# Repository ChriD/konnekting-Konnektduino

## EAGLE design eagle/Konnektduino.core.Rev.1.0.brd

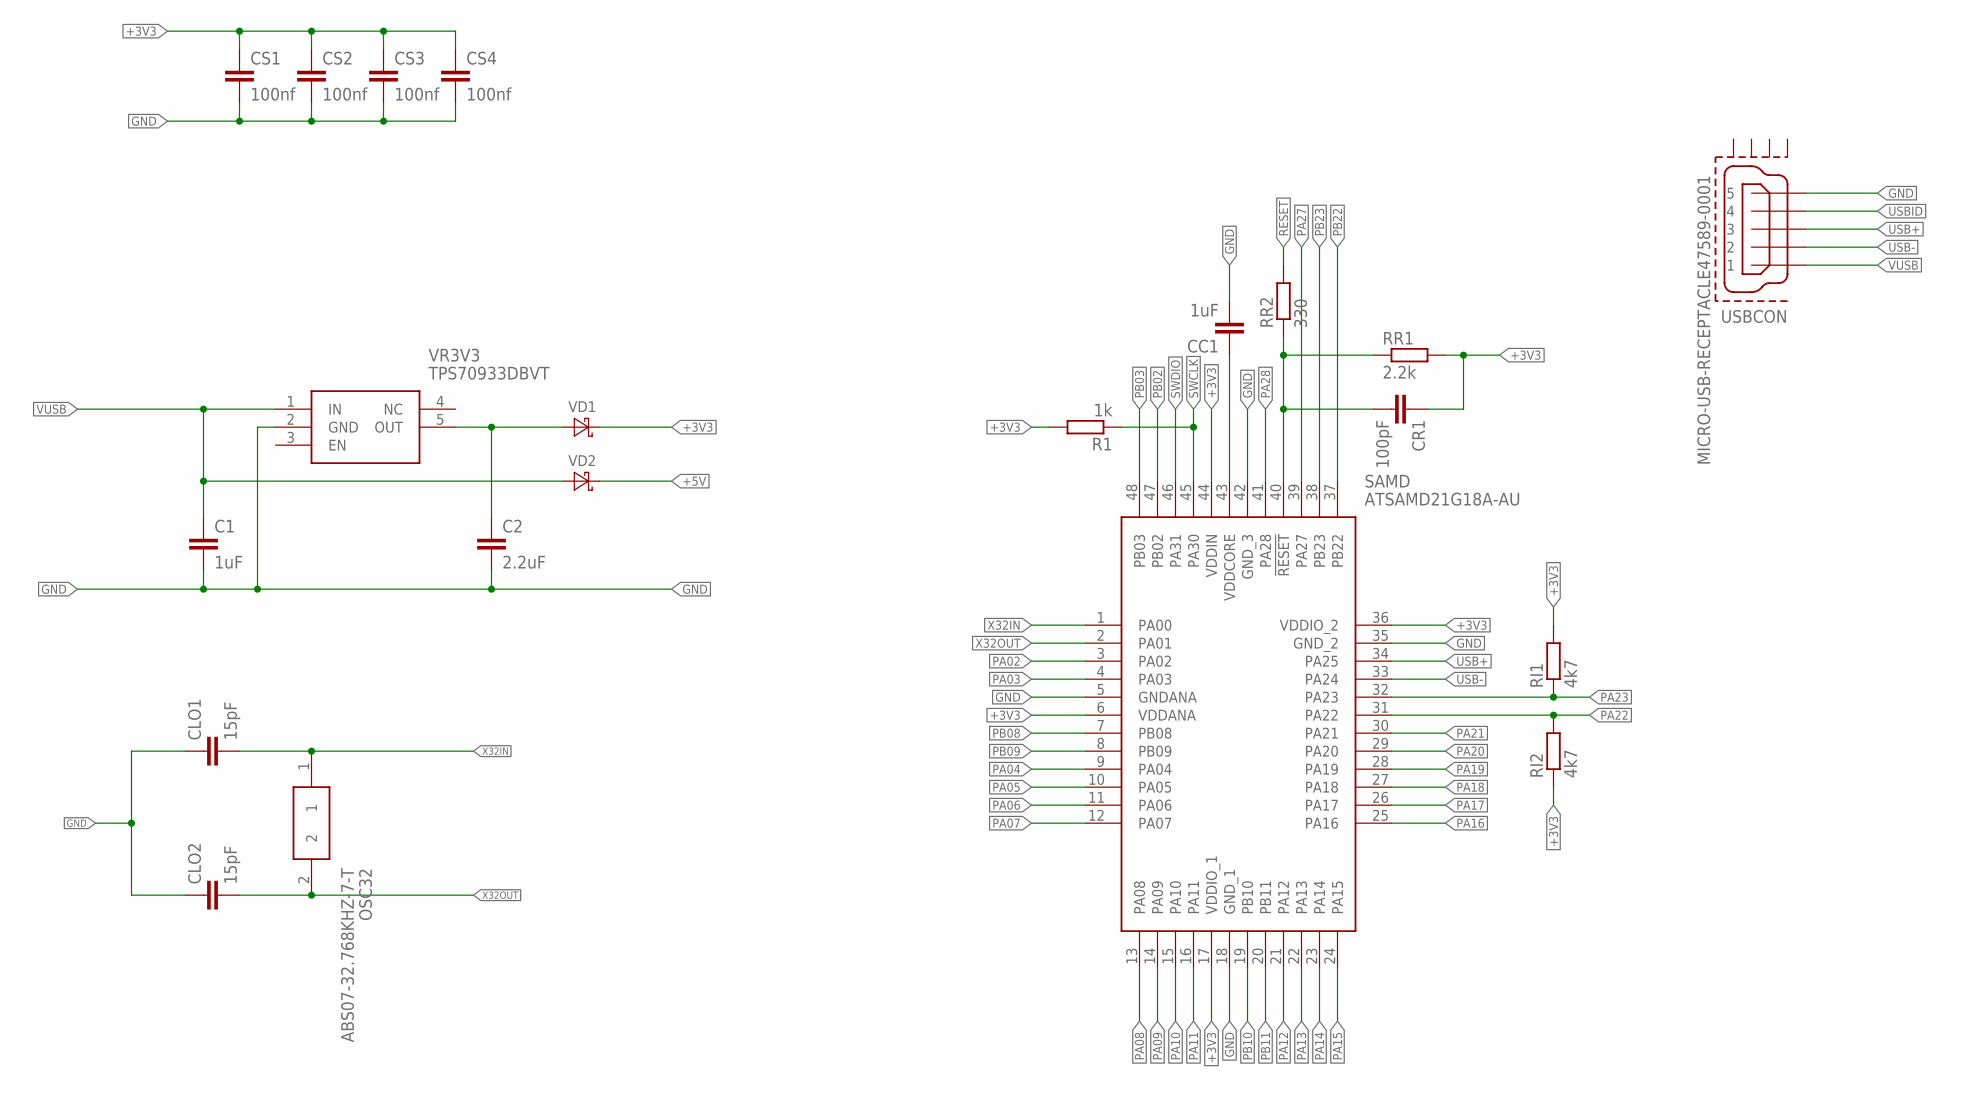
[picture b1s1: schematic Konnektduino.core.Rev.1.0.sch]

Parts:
C1: 1uF; C0603
C2: 2.2uF; C0603
CC1: 1uF; C0603
CLO1, CLO2: 15pF; C0603
CR1: 100pF; C0603
CS1, CS2, CS3, CS4: 100nf; C0603
OSC32: ABS07-32.768KHZ-7-T; ABS-07
R1: 1k; R0603
RI1, RI2: 4k7; R0603
RR1: 2.2k; R0603
RR2: 330; R0603
SAMD: ATSAMD21G18A-AU; QFP50P900X900X120-48N
USBCON: MICRO-USB-RECEPTACLE47589-0001; 47589-0001
VD1, VD2: DIODE-SCHOTTKY-0603; D0603
VR3V3: TPS70933DBVT; SOT95P280X145-5N

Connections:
+3V3: CR1.1, CS1.1, CS2.1, CS3.1, CS4.1, R1.2, RI1.2, RI2.1, RR1.2, SAMD.6 (VDDANA), SAMD.17 (VDDIO_1), SAMD.36 (VDDIO_2), SAMD.44 (VDDIN), VD1.C
+5V: VD2.C
GND: C1.2, C2.2, CC1.2, CLO1.1, CLO2.1, CS1.2, CS2.2, CS3.2, CS4.2, SAMD.5 (GNDANA), SAMD.18 (GND_1), SAMD.35 (GND_2), SAMD.42 (GND_3), USBCON.5, VR3V3.2 (GND)
unnamed: C2.1, VD1.A, VR3V3.5 (OUT)
NRST: CR1.2, RR1.1, RR2.1, SAMD.40 (!RESET)
PA02: SAMD.3 (PA02)
PA03: SAMD.4 (PA03)
PA04: SAMD.9 (PA04)
PA05: SAMD.10 (PA05)
PA06: SAMD.11 (PA06)
PA07: SAMD.12 (PA07)
PA08: SAMD.13 (PA08)
PA09: SAMD.14 (PA09)
PA10: SAMD.15 (PA10)
PA11: SAMD.16 (PA11)
PA12: SAMD.21 (PA12)
PA13: SAMD.22 (PA13)
PA14: SAMD.23 (PA14)
PA15: SAMD.24 (PA15)
PA16: SAMD.25 (PA16)
PA17: SAMD.26 (PA17)
PA18: SAMD.27 (PA18)
PA19: SAMD.28 (PA19)
PA20: SAMD.29 (PA20)
PA21: SAMD.30 (PA21)
PA22: RI2.2, SAMD.31 (PA22)
PA23: RI1.1, SAMD.32 (PA23)
PA27: SAMD.39 (PA27)
PA28: SAMD.41 (PA28)
PB02: SAMD.47 (PB02)
PB03: SAMD.48 (PB03)
PB08: SAMD.7 (PB08)
PB09: SAMD.8 (PB09)
PB10: SAMD.19 (PB10)
PB11: SAMD.20 (PB11)
PB22: SAMD.37 (PB22)
PB23: SAMD.38 (PB23)
RESET: RR2.2
SWCLK: R1.1, SAMD.45 (PA30)
SWDIO: SAMD.46 (PA31)
USB+: SAMD.34 (PA25), USBCON.3
USB-: SAMD.33 (PA24), USBCON.2
USBID: USBCON.4
VDDCORE: CC1.1, SAMD.43 (VDDCORE)
VUSB: C1.1, USBCON.1, VD2.A, VR3V3.1 (IN)
X32IN: CLO1.2, OSC32.1, SAMD.1 (PA00)
X32OUT: CLO2.2, OSC32.2, SAMD.2 (PA01)

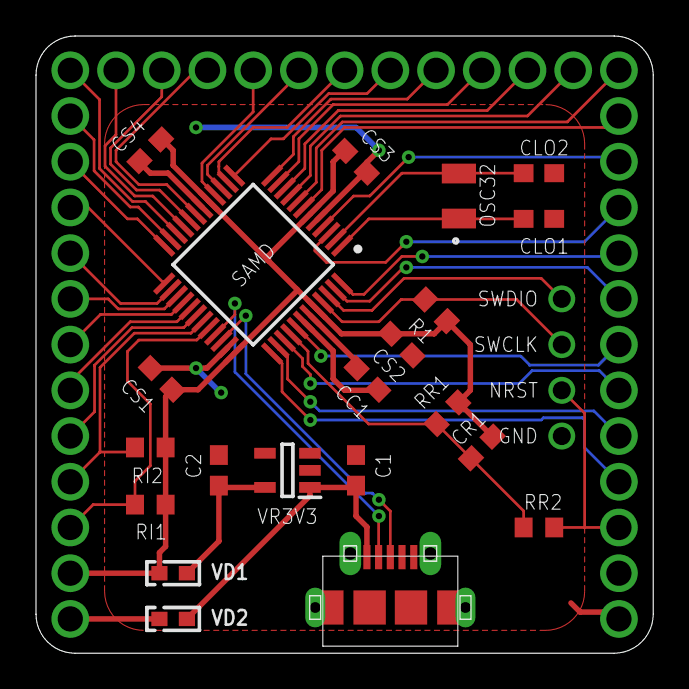
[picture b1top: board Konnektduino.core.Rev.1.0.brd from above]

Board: 2 copper layers, 34.3 x 34.3 mm, 21 parts (0 on the bottom side), 13 nets.

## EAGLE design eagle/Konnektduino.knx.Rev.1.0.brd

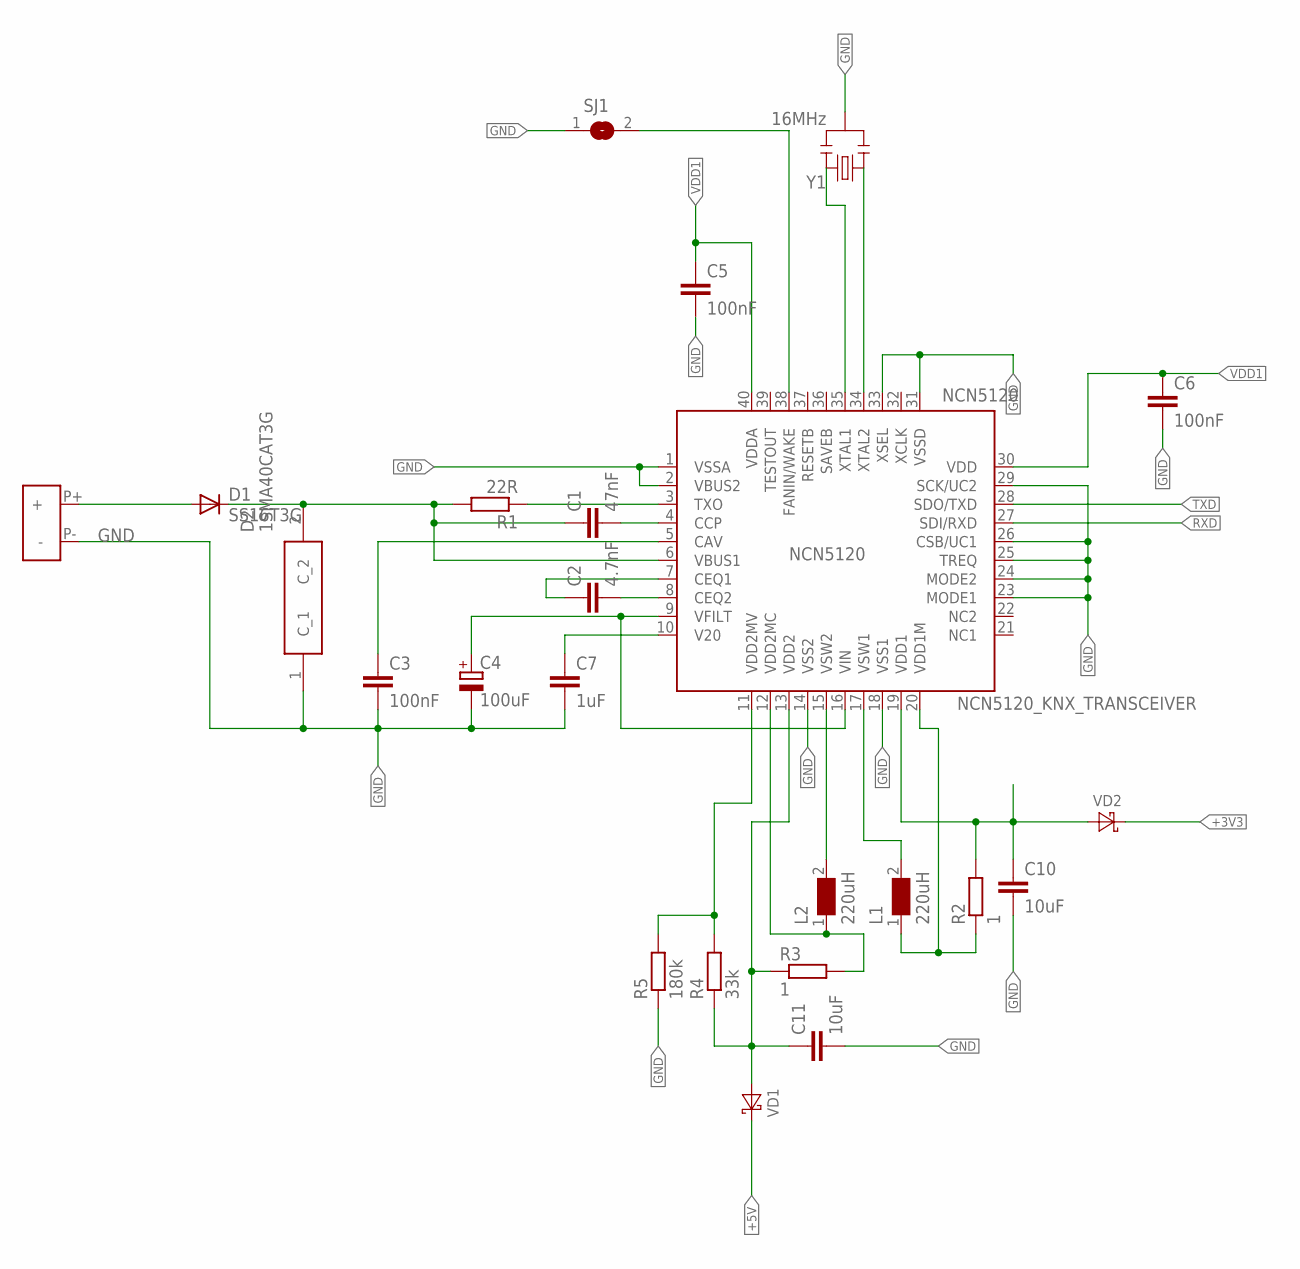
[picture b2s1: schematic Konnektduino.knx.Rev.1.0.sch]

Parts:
C1: 47nF; C0603
C2: 4.7nF; C0603
C3, C5, C6: 100nF; C0603
C4: 100uF; PANASONIC_E
C7: 1uF; C0603
C10, C11: 10uF; C0603
D1: SS16T3G; SMA-DIODE_ALT
D2: 1SMA40CAT3G; DIONM5226X220N
L1, L2: 220uH; WE-PD2_7850
NCN5120: NCN5120_KNX_TRANSCEIVER; QFN40
R1: 22R; R1218
R2, R3: 1; R0603
R4: 33k; R0603
R5: 180k; R0603
SJ1: SJW
U$2: KNX_KLEMME
VD1, VD2: DIODE-SCHOTTKY-0603; D0603
Y1: 16MHz; RESONATOR-SMD

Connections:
+3V3: VD2.C
+5V: VD1.C
GND: C3.2, C4.-, C5.2, C6.2, C7.2, C10.2, C11.2, D2.1 (C_1), NCN5120.1 (VSSA), NCN5120.2 (VBUS2), NCN5120.14 (VSS2), NCN5120.18 (VSS1), NCN5120.23 (MODE1), NCN5120.24 (MODE2), NCN5120.25 (TREQ), NCN5120.26 (CSB/UC1), NCN5120.29 (SCK/UC2), NCN5120.31 (VSSD), NCN5120.33 (XSEL), R5.1, SJ1.1, U$2.P- (-), Y1.2
unnamed: C1.1, D1.C, D2.2 (C_2), NCN5120.6 (VBUS1), R1.2
unnamed: C2.1, NCN5120.7 (CEQ1)
unnamed: C4.+, NCN5120.9 (VFILT), NCN5120.16 (VIN)
unnamed: L2.2, NCN5120.15 (VSW2)
unnamed: C1.2, NCN5120.4 (CCP)
unnamed: C7.1, NCN5120.10 (V20)
unnamed: NCN5120.11 (VDD2MV), R4.2, R5.2
unnamed: L2.1, NCN5120.12 (VDD2MC), R3.2
unnamed: C3.1, NCN5120.5 (CAV)
unnamed: C2.2, NCN5120.8 (CEQ2)
unnamed: NCN5120.38 (FANIN/WAKE), SJ1.2
unnamed: D1.A, U$2.P+ (+)
unnamed: L1.2, NCN5120.17 (VSW1)
unnamed: L1.1, NCN5120.20 (VDD1M), R2.1
unnamed: NCN5120.3 (TXO), R1.1
RXD: NCN5120.27 (SDI/RXD)
TXAL1: NCN5120.35 (XTAL1), Y1.3
TXAL2: NCN5120.34 (XTAL2), Y1.1
TXD: NCN5120.28 (SDO/TXD)
VDD1: C5.1, C6.1, C10.1, NCN5120.19 (VDD1), NCN5120.30 (VDD), NCN5120.40 (VDDA), R2.2, VD2.A
VDD2: C11.1, NCN5120.13 (VDD2), R3.1, R4.1, VD1.A

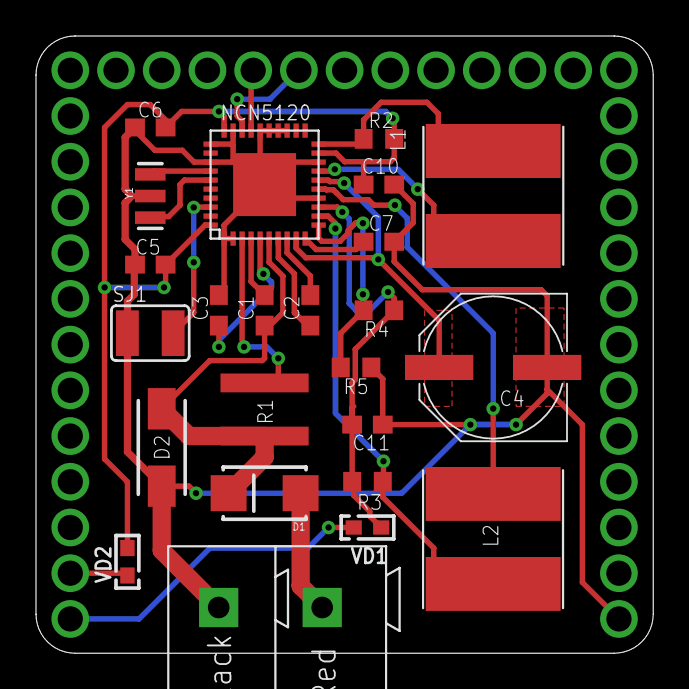
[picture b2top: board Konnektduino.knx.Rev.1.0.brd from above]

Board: 2 copper layers, 34.3 x 34.3 mm, 24 parts (0 on the bottom side), 20 nets.

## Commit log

2018-09-01 Initial
2018-09-01 board updates

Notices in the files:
parts and their libraries:
con-molex-usb: (C) 2014 Tomasz Boleslaw CEDRO, cederom@tlen.pl, http://www.tomek.cedro.info.
Wuerth_PowerMagnetics: Copyright: Würth Elektronik
